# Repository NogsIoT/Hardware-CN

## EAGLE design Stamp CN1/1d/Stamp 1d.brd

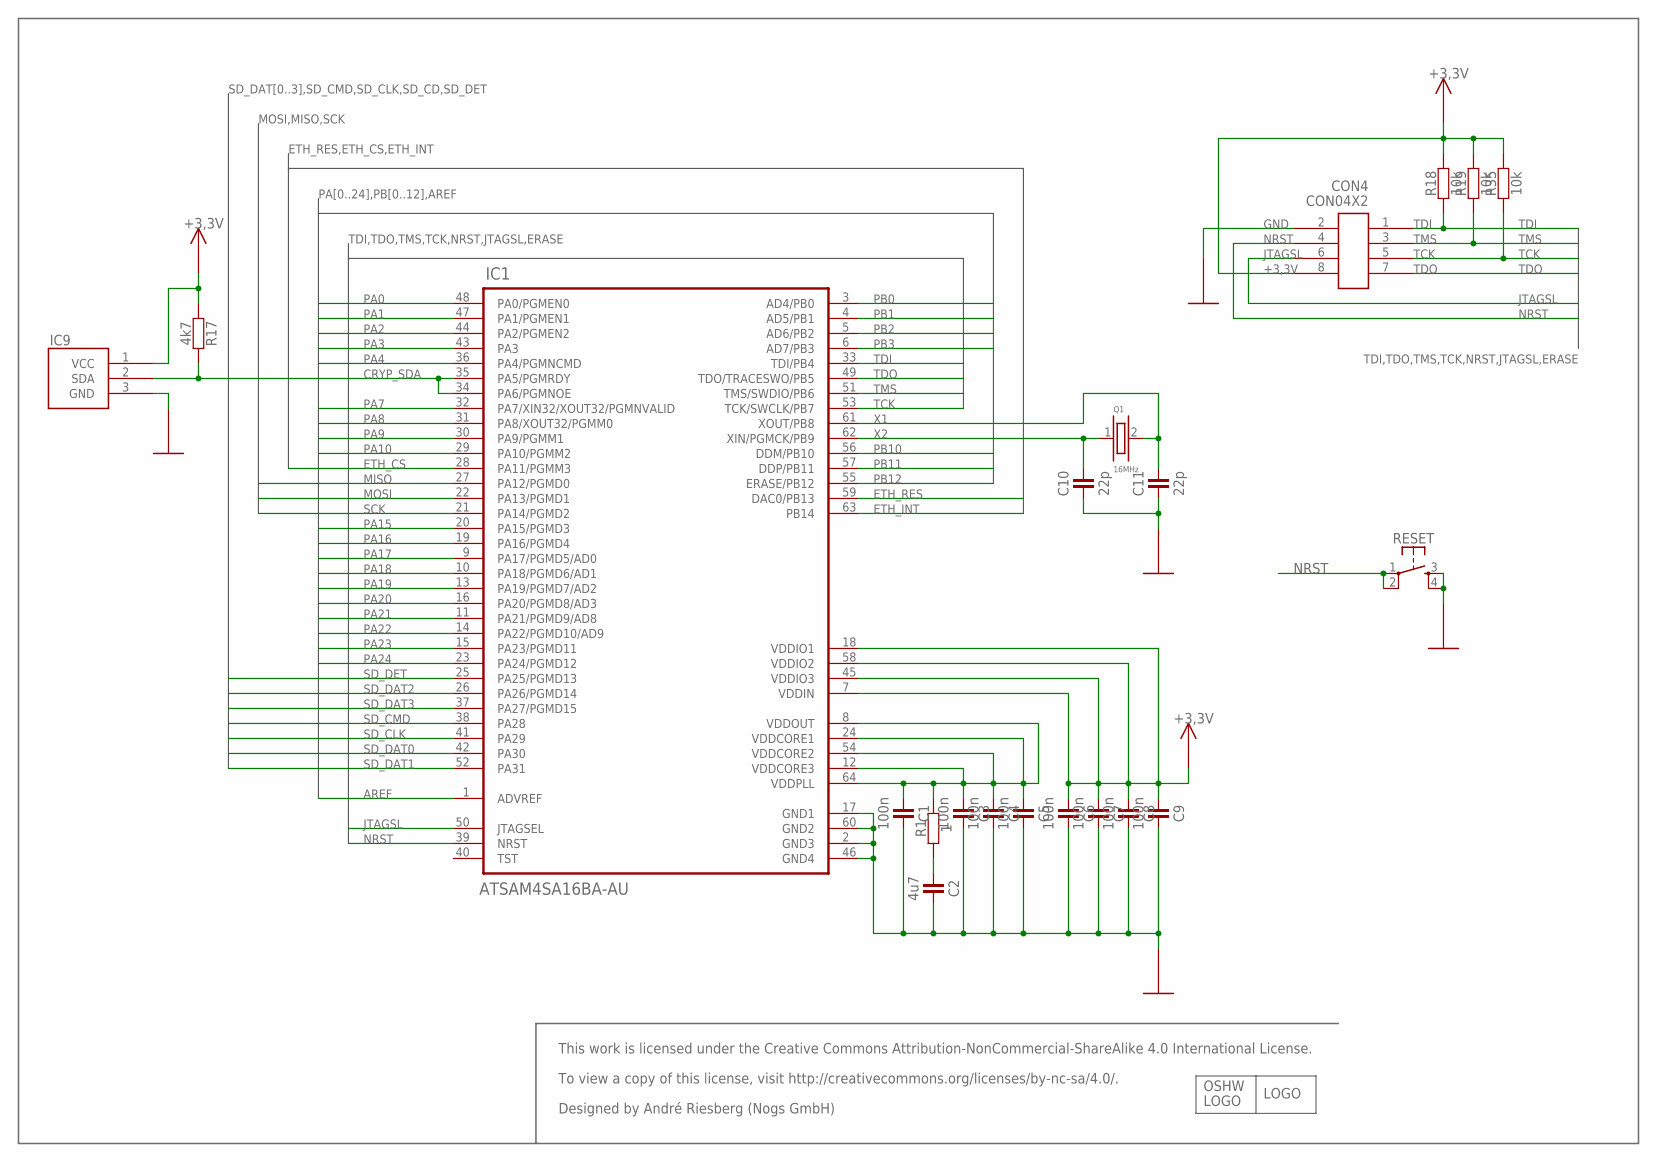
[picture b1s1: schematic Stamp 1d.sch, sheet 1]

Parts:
C1, C3, C4, C5, C6, C7, C8, C9: 100n; R0402
C2: 4u7; R0402
C10, C11: 22p; R0402
CON4: CON04X2
IC1: ATSAM4SA16BA-AU; QFP50P1200X1200X160-64N
IC9: SHA240-1; SOT-23
Q1: 16MHz; TXC1
R1: 1; R0402
R17: 4k7; R0402
R18, R19, R35: 10k; R0402
RESET: SW-TACTILE-PTS840P; SW_PTS840P

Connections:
+1,8V_A: C1.1, C3.1, C4.1, C5.1, IC1.8 (VDDOUT), IC1.12 (VDDCORE3), IC1.24 (VDDCORE1), IC1.54 (VDDCORE2), IC1.64 (VDDPLL), R1.2
+3,3V: C6.1, C7.1, C8.1, C9.1, CON4.8, IC1.7 (VDDIN), IC1.18 (VDDIO1), IC1.45 (VDDIO3), IC1.58 (VDDIO2), IC9.1 (VCC), R17.1, R18.2, R19.2, R35.2; also elsewhere on the board
AREF: IC1.1 (ADVREF); also elsewhere on the board
CRYP_SDA: IC1.34 (PA6/PGMNOE), IC1.35 (PA5/PGMRDY), IC9.2 (SDA), R17.2
ETH_CS: IC1.28 (PA11/PGMM3); also elsewhere on the board
ETH_INT: IC1.63 (PB14); also elsewhere on the board
ETH_RES: IC1.59 (DAC0/PB13); also elsewhere on the board
GND: C1.2, C2.2, C3.2, C4.2, C5.2, C6.2, C7.2, C8.2, C9.2, C10.1, C11.1, CON4.2, IC1.2 (GND3), IC1.17 (GND1), IC1.46 (GND4), IC1.60 (GND2), IC9.3 (GND), RESET.3 (S1), RESET.4 (S2); also elsewhere on the board
JTAGSL: CON4.6, IC1.50 (JTAGSEL)
MISO: IC1.27 (PA12/PGMD0); also elsewhere on the board
MOSI: IC1.22 (PA13/PGMD1); also elsewhere on the board
unnamed: C2.1, R1.1
NRST: CON4.4, IC1.39 (NRST), RESET.1, RESET.2
PA0: IC1.48 (PA0/PGMEN0); also elsewhere on the board
PA1: IC1.47 (PA1/PGMEN1); also elsewhere on the board
PA2: IC1.44 (PA2/PGMEN2); also elsewhere on the board
PA3: IC1.43 (PA3); also elsewhere on the board
PA4: IC1.36 (PA4/PGMNCMD); also elsewhere on the board
PA7: IC1.32 (PA7/XIN32/XOUT32/PGMNVALID); also elsewhere on the board
PA8: IC1.31 (PA8/XOUT32/PGMM0); also elsewhere on the board
PA9: IC1.30 (PA9/PGMM1); also elsewhere on the board
PA10: IC1.29 (PA10/PGMM2); also elsewhere on the board
PA15: IC1.20 (PA15/PGMD3); also elsewhere on the board
PA16: IC1.19 (PA16/PGMD4); also elsewhere on the board
PA17: IC1.9 (PA17/PGMD5/AD0); also elsewhere on the board
PA18: IC1.10 (PA18/PGMD6/AD1); also elsewhere on the board
PA19: IC1.13 (PA19/PGMD7/AD2); also elsewhere on the board
PA20: IC1.16 (PA20/PGMD8/AD3); also elsewhere on the board
PA21: IC1.11 (PA21/PGMD9/AD8); also elsewhere on the board
PA22: IC1.14 (PA22/PGMD10/AD9); also elsewhere on the board
PA23: IC1.15 (PA23/PGMD11); also elsewhere on the board
PA24: IC1.23 (PA24/PGMD12); also elsewhere on the board
PB0: IC1.3 (AD4/PB0); also elsewhere on the board
PB1: IC1.4 (AD5/PB1); also elsewhere on the board
PB2: IC1.5 (AD6/PB2); also elsewhere on the board
PB3: IC1.6 (AD7/PB3); also elsewhere on the board
PB10: IC1.56 (DDM/PB10); also elsewhere on the board
PB11: IC1.57 (DDP/PB11); also elsewhere on the board
PB12: IC1.55 (ERASE/PB12); also elsewhere on the board
SCK: IC1.21 (PA14/PGMD2); also elsewhere on the board
SD_CLK: IC1.41 (PA29); also elsewhere on the board
SD_CMD: IC1.38 (PA28); also elsewhere on the board
SD_DAT0: IC1.42 (PA30); also elsewhere on the board
SD_DAT1: IC1.52 (PA31); also elsewhere on the board
SD_DAT2: IC1.26 (PA26/PGMD14); also elsewhere on the board
SD_DAT3: IC1.37 (PA27/PGMD15); also elsewhere on the board
SD_DET: IC1.25 (PA25/PGMD13); also elsewhere on the board
TCK: CON4.5, IC1.53 (TCK/SWCLK/PB7), R35.1
TDI: CON4.1, IC1.33 (TDI/PB4), R18.1
TDO: CON4.7, IC1.49 (TDO/TRACESWO/PB5)
TMS: CON4.3, IC1.51 (TMS/SWDIO/PB6), R19.1
X1: C11.2, IC1.61 (XOUT/PB8), Q1.2
X2: C10.2, IC1.62 (XIN/PGMCK/PB9), Q1.1

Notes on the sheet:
To view a copy of this license, visit http://creativecommons.org/licenses/by-nc-sa/4.0/.
Designed by André Riesberg (Nogs GmbH)
This work is licensed under the Creative Commons Attribution-NonCommercial-ShareAlike 4.0 International License.
OSHW
LOGO

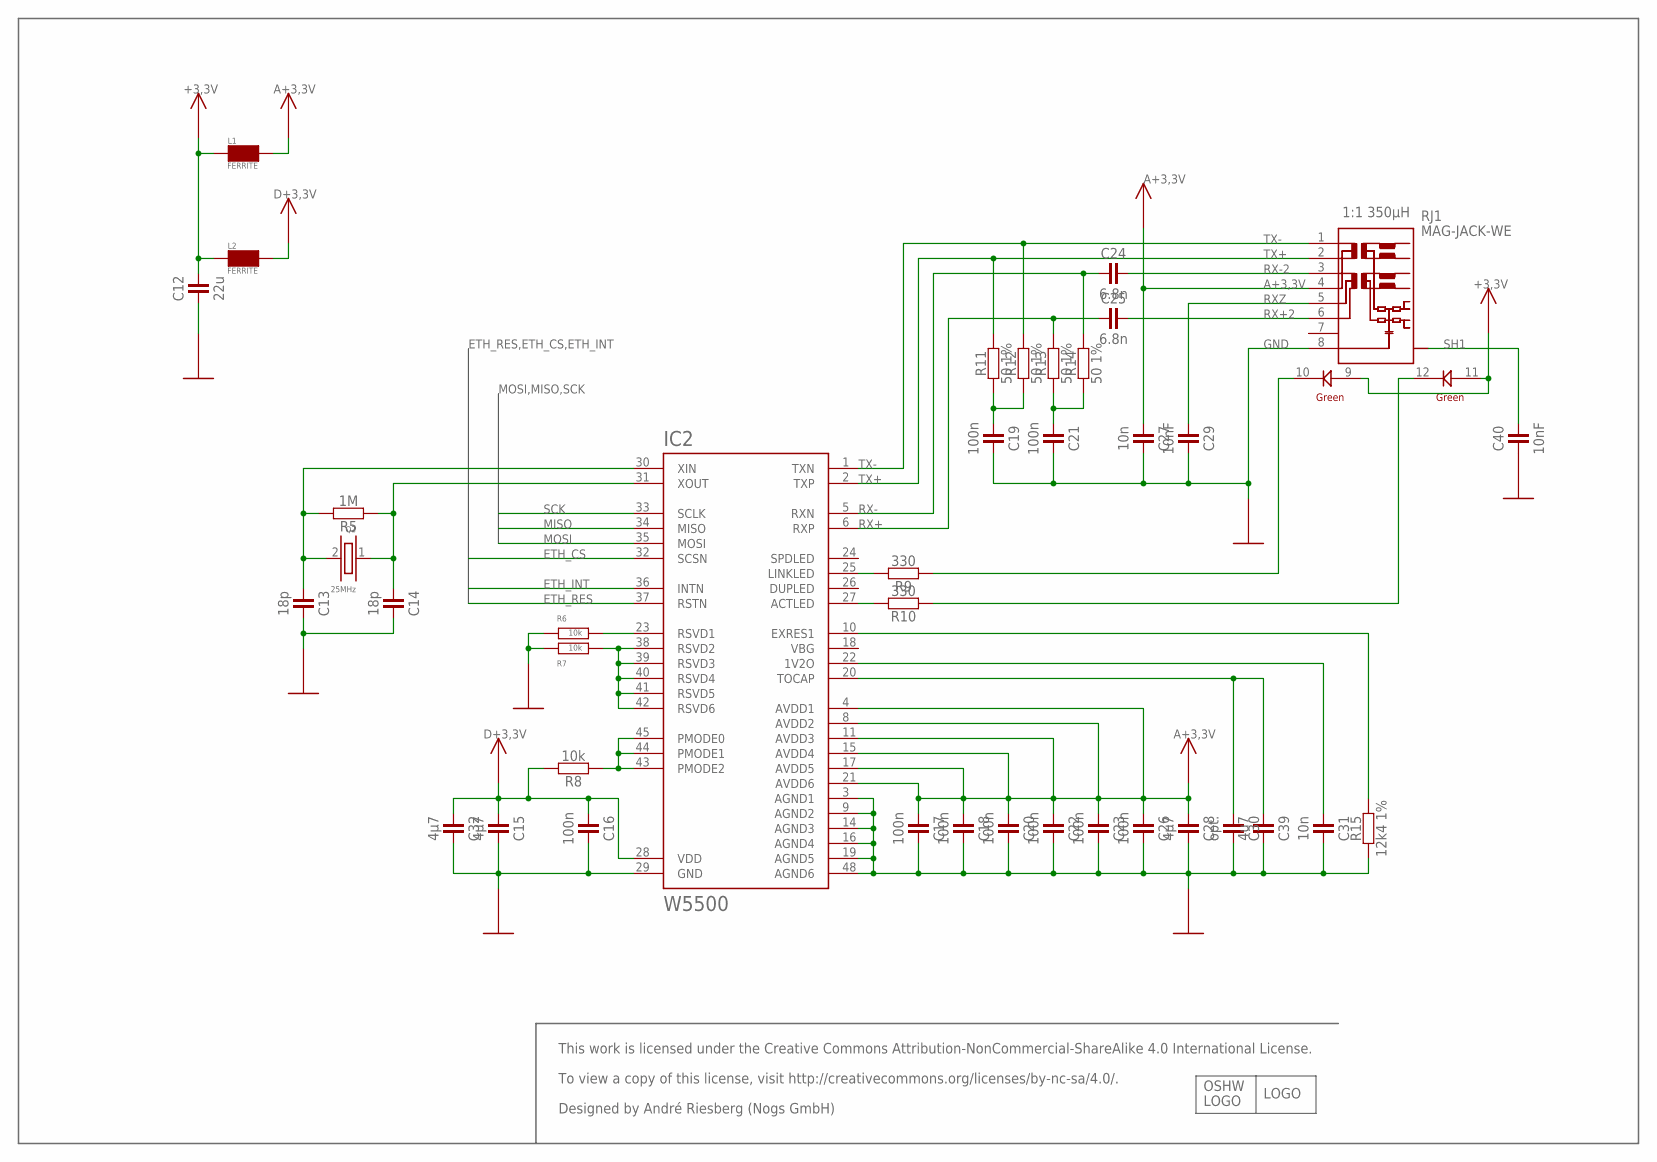
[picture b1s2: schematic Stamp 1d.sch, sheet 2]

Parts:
C12: 22u; R1206
C13, C14: 18p; R0402
C15, C28, C32: 4µ7; R0402
C16, C17, C18, C19, C20, C21, C22, C23, C26: 100n; R0402
C24, C25: 6.8n; R0402
C27, C31: 10n; R0402
C29, C40: 10nF; R0402
C30: opt.; R0402
C39: 4u7; R0402
IC2: W5500; LQFP-48
L1, L2: FERRITE; 1206@2
Q2: 25MHz; TXC1
R5: 1M; R0402
R6, R7, R8: 10k; R0402
R9, R10: 330; R0402
R11, R12, R13, R14: 50 1%; R0402
R15: 12k4 1%; R0402
RJ1: MAG-JACK-WE; 7499011121A

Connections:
+3,3V: C12.2, L1.1, L2.1, RJ1.9, RJ1.11; also elsewhere on the board
A+3,3V: C17.1, C18.1, C20.1, C22.1, C23.1, C26.1, C27.1, C28.1, IC2.4 (AVDD1), IC2.8 (AVDD2), IC2.11 (AVDD3), IC2.15 (AVDD4), IC2.17 (AVDD5), IC2.21 (AVDD6), L1.2, RJ1.4
D+3,3V: C15.1, C16.1, C32.1, IC2.28 (VDD), L2.2, R8.2
ETH_CS: IC2.32 (SCSN); also elsewhere on the board
ETH_INT: IC2.36 (INTN); also elsewhere on the board
ETH_RES: IC2.37 (RSTN); also elsewhere on the board
GND: C12.1, C13.1, C14.1, C15.2, C16.2, C17.2, C18.2, C19.2, C20.2, C21.2, C22.2, C23.2, C26.2, C27.2, C28.2, C29.2, C30.2, C31.2, C32.2, C39.2, C40.1, IC2.3 (AGND1), IC2.9 (AGND2), IC2.14 (AGND3), IC2.16 (AGND4), IC2.19 (AGND5), IC2.29 (GND), IC2.48 (AGND6), R6.2, R7.2, R15.1, RJ1.8; also elsewhere on the board
MISO: IC2.34 (MISO); also elsewhere on the board
MOSI: IC2.35 (MOSI); also elsewhere on the board
unnamed: IC2.25 (LINKLED), R9.2
unnamed: IC2.43 (PMODE2), IC2.44 (PMODE1), IC2.45 (PMODE0), R8.1
unnamed: C14.2, IC2.31 (XOUT), Q2.1, R5.2
unnamed: C13.2, IC2.30 (XIN), Q2.2, R5.1
unnamed: IC2.23 (RSVD1), R6.1
unnamed: IC2.27 (ACTLED), R10.2
unnamed: IC2.38 (RSVD2), IC2.39 (RSVD3), IC2.40 (RSVD4), IC2.41 (RSVD5), IC2.42 (RSVD6), R7.1
unnamed: IC2.10 (EXRES1), R15.2
unnamed: C31.1, IC2.22 (1V2O)
unnamed: C30.1, C39.1, IC2.20 (TOCAP)
unnamed: C19.1, R11.1, R12.1
unnamed: C21.1, R13.1, R14.1
unnamed: R9.1, RJ1.10
unnamed: R10.1, RJ1.12
RX+: C25.1, IC2.6 (RXP), R13.2
RX+2: C25.2, RJ1.6
RX-: C24.1, IC2.5 (RXN), R14.2
RX-2: C24.2, RJ1.3
RXZ: C29.1, RJ1.5
SCK: IC2.33 (SCLK); also elsewhere on the board
SH1: C40.2, RJ1.SH@1 (S), RJ1.SH@2 (S)
TX+: IC2.2 (TXP), R11.2, RJ1.2
TX-: IC2.1 (TXN), R12.2, RJ1.1
VBG: IC2.18 (VBG)

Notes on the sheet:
1:1 350µH
To view a copy of this license, visit http://creativecommons.org/licenses/by-nc-sa/4.0/.
Designed by André Riesberg (Nogs GmbH)
This work is licensed under the Creative Commons Attribution-NonCommercial-ShareAlike 4.0 International License.
OSHW
LOGO

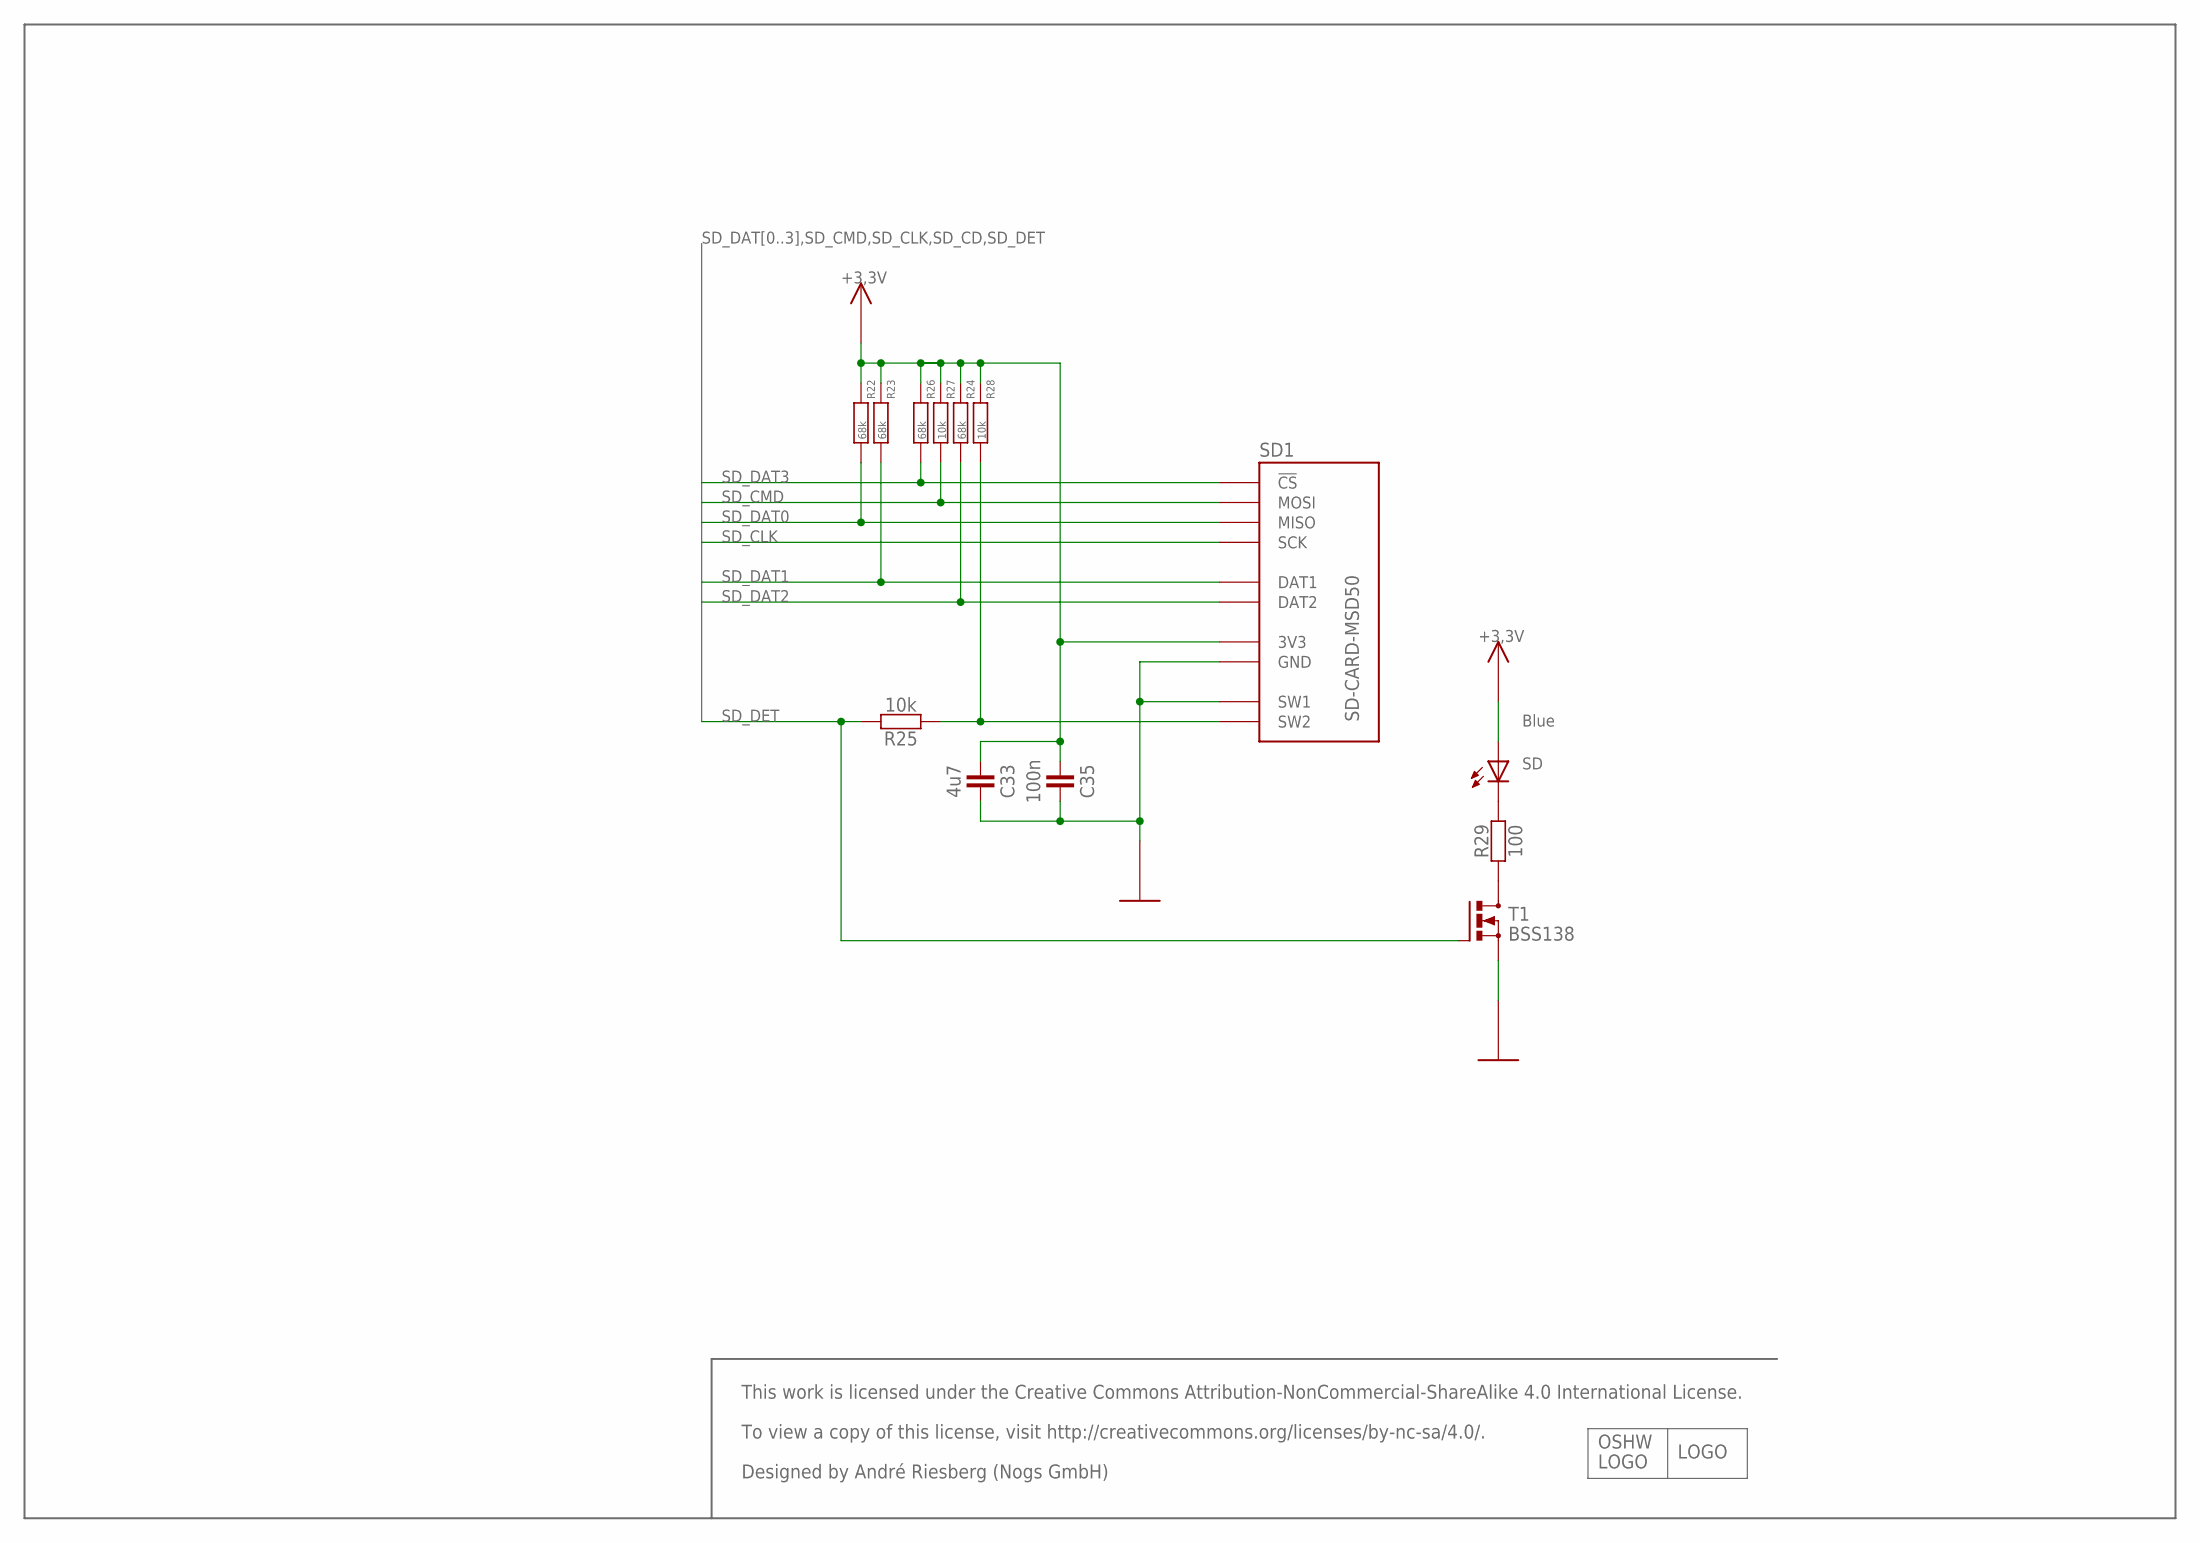
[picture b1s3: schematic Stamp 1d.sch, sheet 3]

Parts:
C33: 4u7; R0402
C35: 100n; R0402
R22, R23, R24, R26: 68k; R0402
R25, R27, R28: 10k; R0402
R29: 100; R0402
SD: Blue; LED_0603
SD1: SD-CARD-MSD50; SD_5031821853
T1: BSS138; SOT23

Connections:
+3,3V: C33.1, C35.1, R22.2, R23.2, R24.2, R26.2, R27.2, R28.2, SD.A, SD1.VCC (3V3); also elsewhere on the board
GND: C33.2, C35.2, SD1.GND, SD1.SW1, T1.2 (S); also elsewhere on the board
unnamed: R29.1, T1.3 (D)
unnamed: R29.2, SD.C
unnamed: R25.1, R28.1, SD1.SW2
SD_CLK: SD1.SCK; also elsewhere on the board
SD_CMD: R27.1, SD1.MOSI; also elsewhere on the board
SD_DAT0: R22.1, SD1.MISO; also elsewhere on the board
SD_DAT1: R23.1, SD1.DAT1; also elsewhere on the board
SD_DAT2: R24.1, SD1.DAT2; also elsewhere on the board
SD_DAT3: R26.1, SD1.CS (!CS); also elsewhere on the board
SD_DET: R25.2, T1.1 (G); also elsewhere on the board

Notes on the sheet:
To view a copy of this license, visit http://creativecommons.org/licenses/by-nc-sa/4.0/.
Designed by André Riesberg (Nogs GmbH)
This work is licensed under the Creative Commons Attribution-NonCommercial-ShareAlike 4.0 International License.
OSHW
LOGO

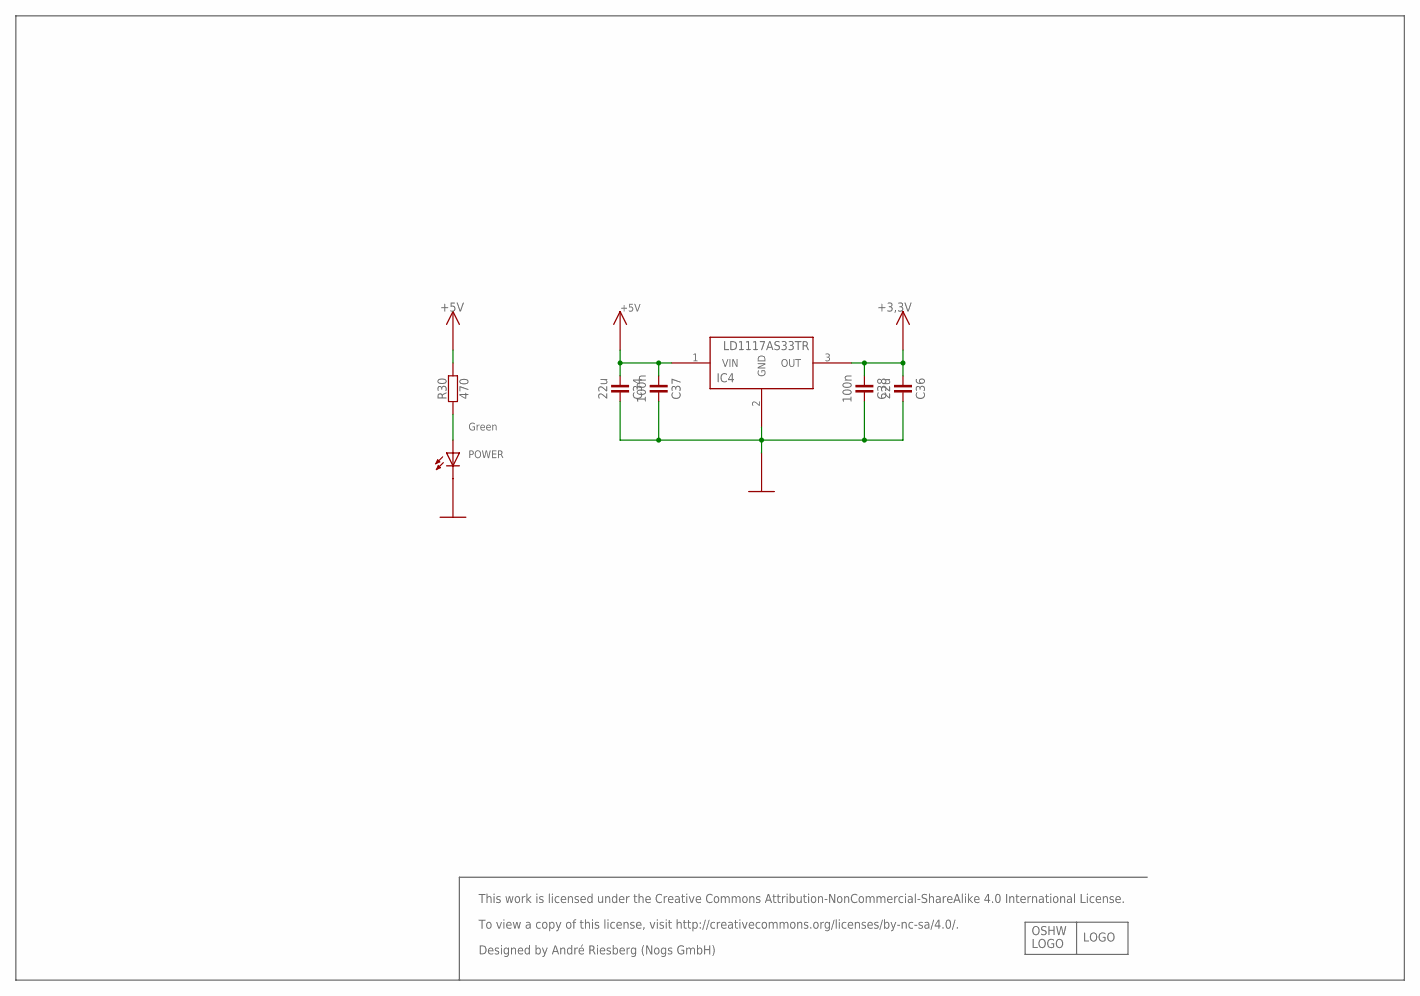
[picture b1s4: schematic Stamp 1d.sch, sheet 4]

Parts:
C34, C36: 22u; R1206
C37, C38: 100n; R0402
IC4: LD1117AS33TR; SOT-223B
POWER: Green; LED_0603
R30: 470; R0402

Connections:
+3,3V: C36.1, C38.1, IC4.3 (OUT); also elsewhere on the board
+5V: C34.1, C37.1, IC4.1 (VIN), R30.2; also elsewhere on the board
GND: C34.2, C36.2, C37.2, C38.2, IC4.2 (GND), POWER.C; also elsewhere on the board
unnamed: POWER.A, R30.1

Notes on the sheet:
To view a copy of this license, visit http://creativecommons.org/licenses/by-nc-sa/4.0/.
Designed by André Riesberg (Nogs GmbH)
This work is licensed under the Creative Commons Attribution-NonCommercial-ShareAlike 4.0 International License.
OSHW
LOGO

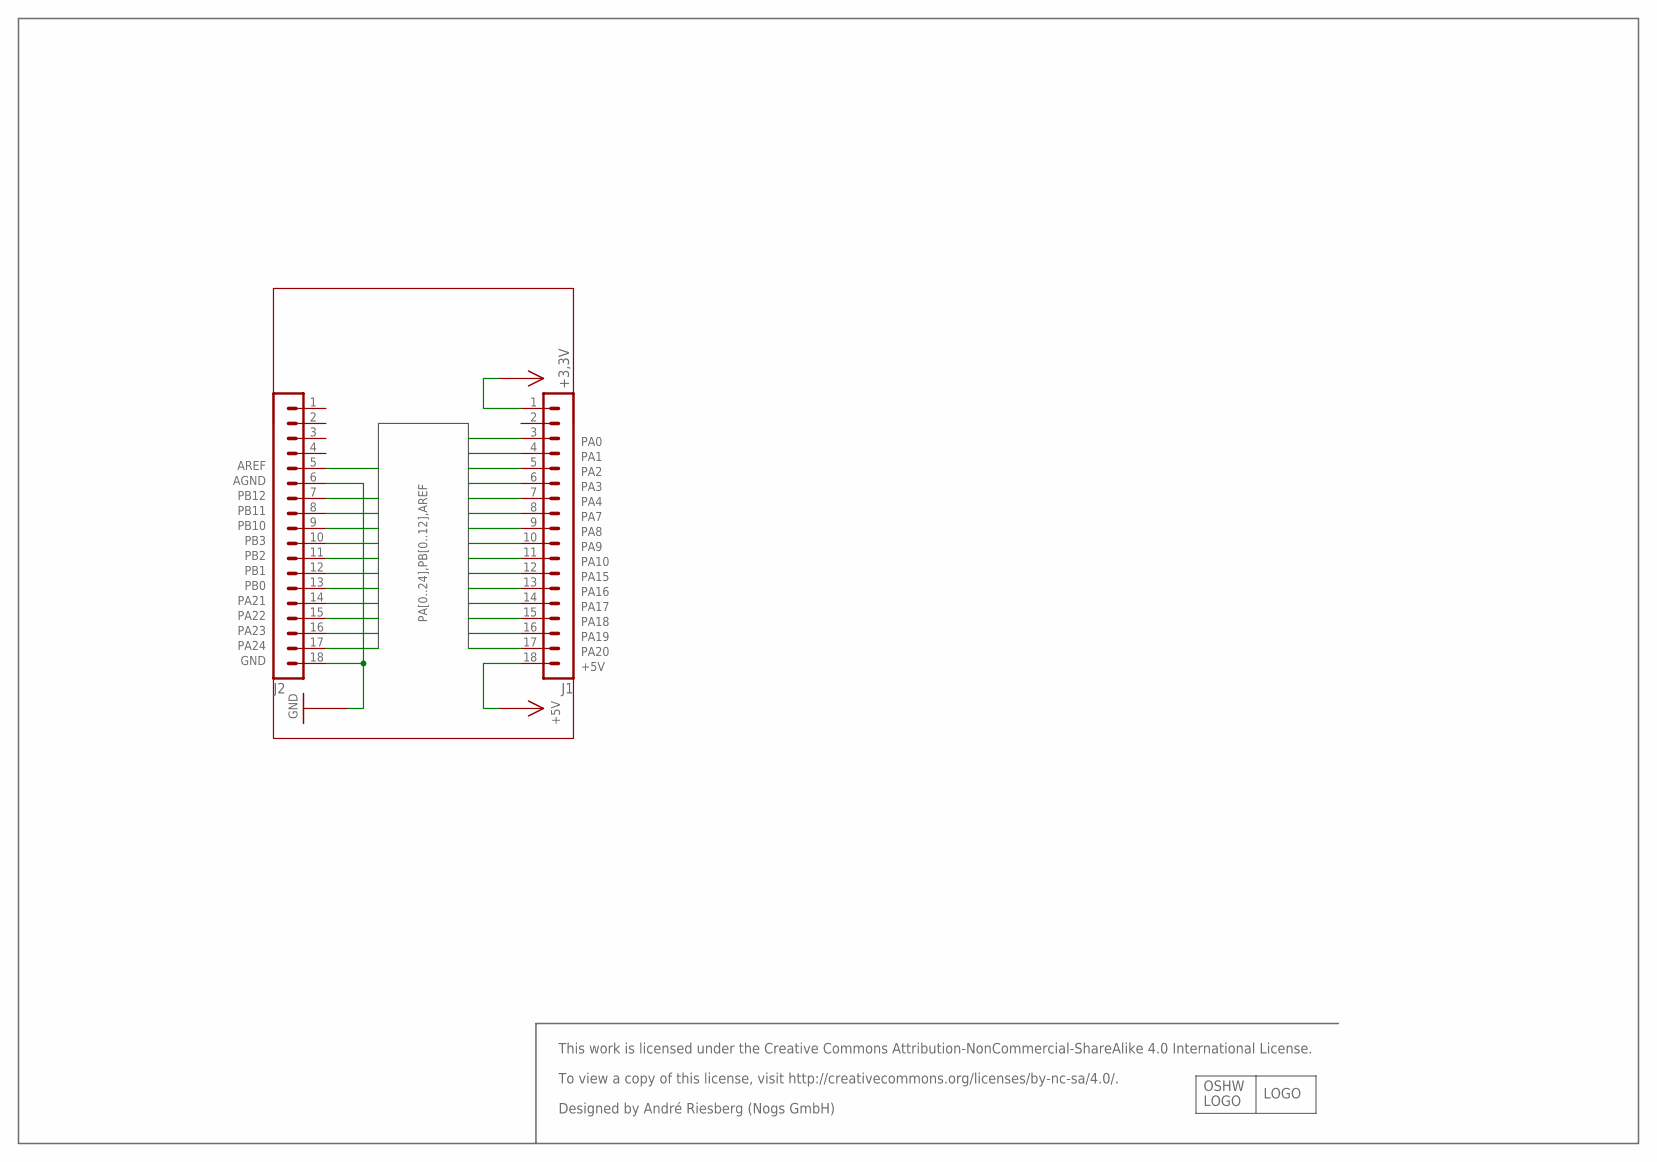
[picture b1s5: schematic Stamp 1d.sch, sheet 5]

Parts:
J1, J2: MA18-1

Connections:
+3,3V: J1.1; also elsewhere on the board
+5V: J1.18; also elsewhere on the board
AREF: J2.5; also elsewhere on the board
GND: J2.6, J2.18; also elsewhere on the board
PA0: J1.3; also elsewhere on the board
PA1: J1.4; also elsewhere on the board
PA2: J1.5; also elsewhere on the board
PA3: J1.6; also elsewhere on the board
PA4: J1.7; also elsewhere on the board
PA7: J1.8; also elsewhere on the board
PA8: J1.9; also elsewhere on the board
PA9: J1.10; also elsewhere on the board
PA10: J1.11; also elsewhere on the board
PA15: J1.12; also elsewhere on the board
PA16: J1.13; also elsewhere on the board
PA17: J1.14; also elsewhere on the board
PA18: J1.15; also elsewhere on the board
PA19: J1.16; also elsewhere on the board
PA20: J1.17; also elsewhere on the board
PA21: J2.14; also elsewhere on the board
PA22: J2.15; also elsewhere on the board
PA23: J2.16; also elsewhere on the board
PA24: J2.17; also elsewhere on the board
PB0: J2.13; also elsewhere on the board
PB1: J2.12; also elsewhere on the board
PB2: J2.11; also elsewhere on the board
PB3: J2.10; also elsewhere on the board
PB10: J2.9; also elsewhere on the board
PB11: J2.8; also elsewhere on the board
PB12: J2.7; also elsewhere on the board

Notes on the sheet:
AGND
To view a copy of this license, visit http://creativecommons.org/licenses/by-nc-sa/4.0/.
Designed by André Riesberg (Nogs GmbH)
This work is licensed under the Creative Commons Attribution-NonCommercial-ShareAlike 4.0 International License.
OSHW
LOGO

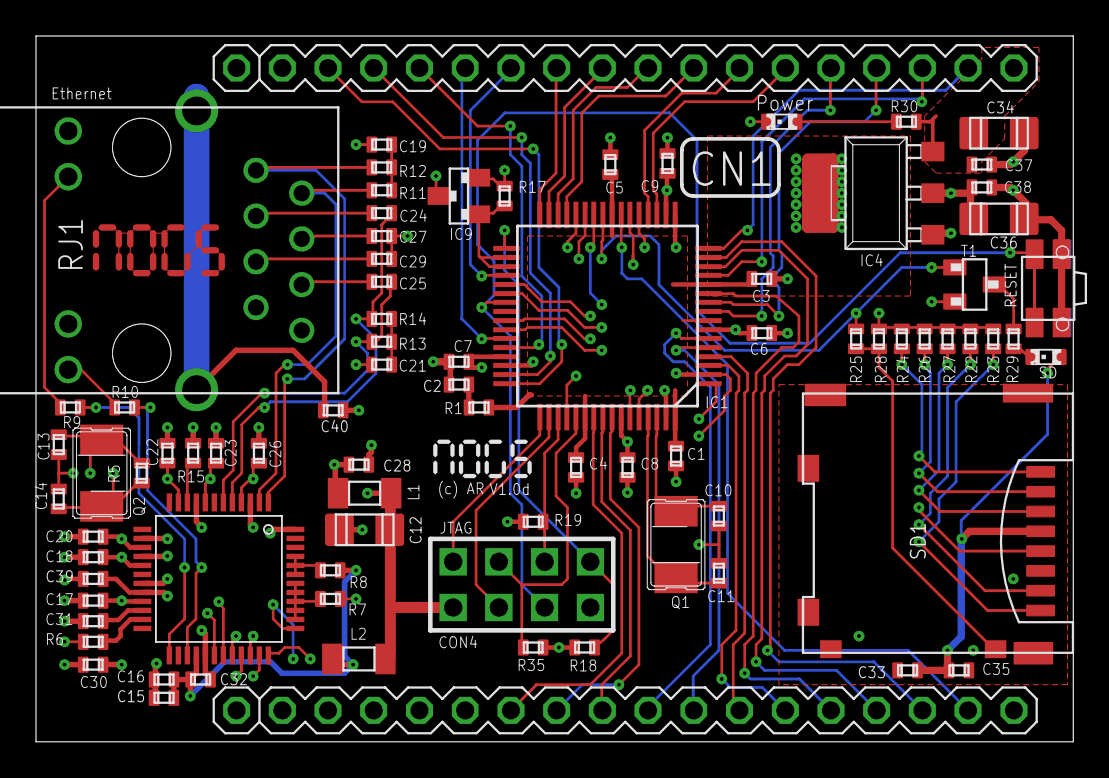
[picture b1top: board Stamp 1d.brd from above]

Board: 4 copper layers, 57.6 x 39.2 mm, 82 parts (0 on the bottom side), 82 nets.

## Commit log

2016-01-25 added eagle schematic and board
